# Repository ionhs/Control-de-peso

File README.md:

# PISU KONTROLA / CONTROL DE PESO

Este es el primer circuito que monta el alumnado de [Don Bosco](https://www.donbosco.eus/elektronika-mantentzen-lana/) en el ciclo de grado superior de Mantenimiento Electrónico. En vez de montar sobre una PCB, el alumnado lo monta sobre una protoboard.

Esto es parte del primer reto, en el que el alumnado sin ningún conocimiento previo ha de diseñar un sistema digital de control de peso con **4 sensores**. Cuanto más peso haya, se irán pulsando más botones hasta alcanzar la cantidad de peso optima, en el que se encenderá un **led verde.** En el caso que el peso no sea adecuado (por exceso o por defecto) se encenderá un **led rojo**. En el caso que la señal de entrada de los botones no sea lógica, se considerará que hay una avería que se indicará mediante un **led naraja**.

En este reto se busca que alumnado adquiera competencias y conocimientos en:

- Señales digitales 1/0 de entrada y de salida.

- Puertas lógicas (not, and, or...).

- Ecuaciones lógicas.

- Método de simplificación de ecuaciones con Karnaugh.

- Montaje y simulación de circuitos con puertas lógicas.

- Mantenimiento de circuitos con puertas lógicas.

El diseño ha sido realizado en [KiCad](https://www.kicad.org/), un software **open source**. Esto permite que cualquiera pueda replicar el proyecto o modificarlo según sus necesidades, facilitando su adaptación a otros usos educativos o personales.

## Puesta en marcha

Para hacer una demostración y la puesta en marcha hay que seguir los siguientes pasos:

1. Dejar la placa sobre la mesa, sin que ningún objeto metálico tenga contacto por la parte de abajo.

2. Mediante un cable usb conectar la placa a una fuente de alimentación usb o un portátil.

En este momento la placa ya es funcional por lo que se puede hacer la siguiente demostración de funcionamiento:

1. Pulsar el botón A y luego A y B a la vez para demostrar que con poco peso se enciende el diodo led de peso no adecuado.

2. Pulsar los botones A, B y C a la vez para demostrar que con peso adecuado se enciende el diodo led de peso adecuado.

3. Pulsar los cuatro botones a la vez para demostrar que con peso excesivo se enciende el diodo led de peso no adecuado.

4. Para demostrar la avería hay que pulsar alguna de las combinaciones imposibles como pulsar sólo B, sólo C, sólo D, sólo B y C a la vez, sólo B y D a la vez, sólo C y D a la vez o sólo B y C y D a la vez. En estos casos se encenderá avería y puede que algunos de los otros dos diodos leds. Como se enciende avería sólo se hace caso a la avería por lo que los otros led diodos no avisarían de nada.

Se puede mostrar la parte de electrónica analógica del reto. Para ello habría que tener una placa con resistencias en serie y paralelo que den 220 ohms de resistencia equivalente. Para conectarla hay que seguir estos pasos:

1. Quitar el jumper (JP1, JP2 o JP3) de la la resistencia interna de la placa que se quiere anular para conectar una equivalente por fuera.

2. Conectar al conector (J2, J3 o J4) la placa de resistencias equivalentes.

3. Probar los puntos 1, 2, 3, 4 de la demostración de funcionamiento.

4. 

## Puntos a mejorar

La placa de alimentación usb hay que ponerla por la parte de abajo para que vcc y gnd estén adecuadamente posicionada. Si se quiere que el USB esté por encima de la PCB habría que modificar el layout dándole la vuelta a la placa de alimentación USB y cambiando el routeo de los dos pads.

Además como mejora se puede diseñar una PCB de una fuente de alimentación de 5v. En la salida se pondría una placa de alimentación USB y mediante un cable, se podría conectar la placa de alimentación, al circuito del control de peso.

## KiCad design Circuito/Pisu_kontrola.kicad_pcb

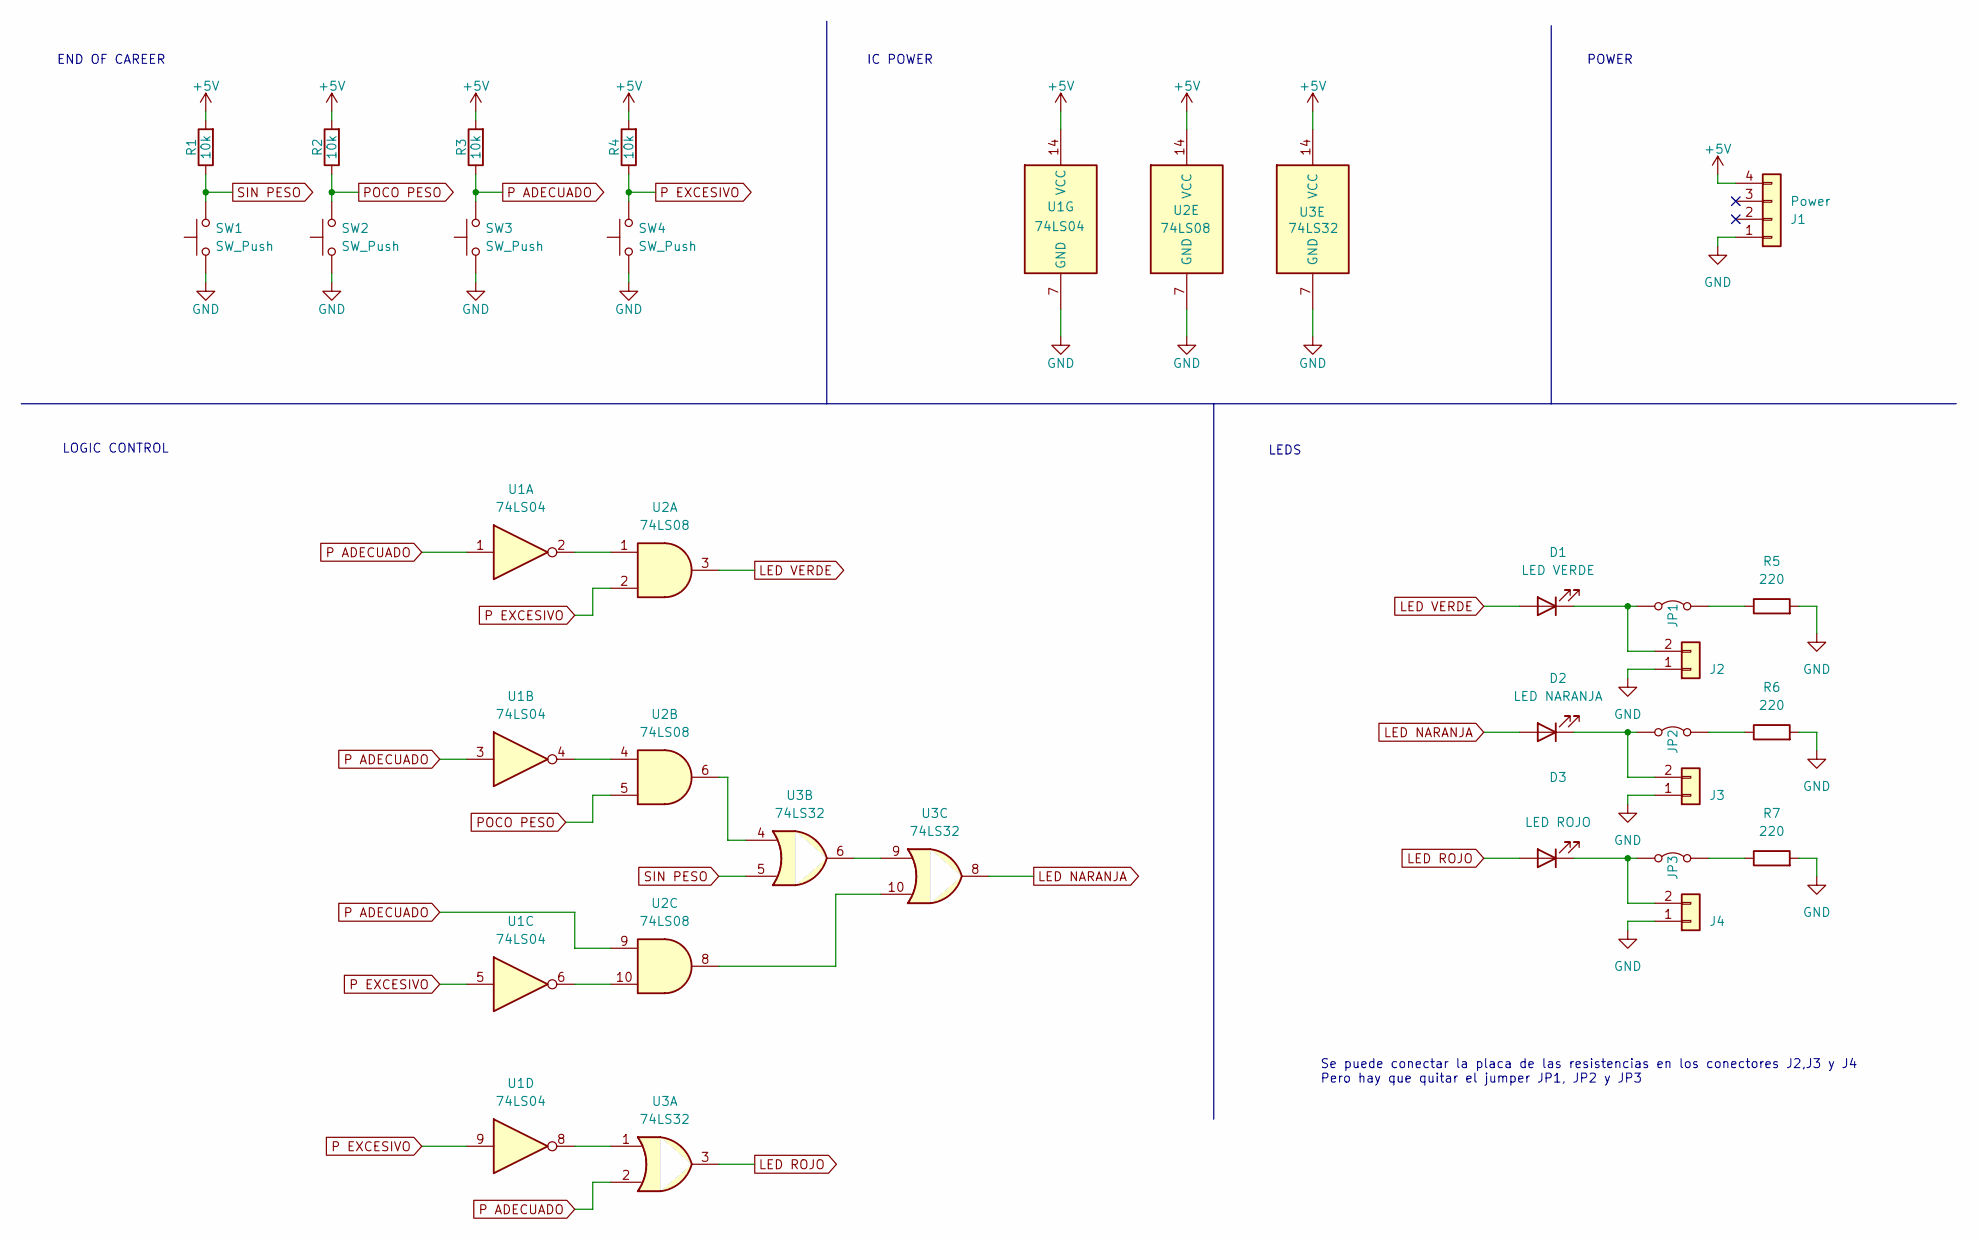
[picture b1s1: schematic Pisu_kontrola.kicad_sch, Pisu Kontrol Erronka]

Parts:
D1: LED VERDE; LED_D5.0mm
D2: LED NARANJA; LED_D5.0mm
D3: LED ROJO; LED_D5.0mm
J1: Power; USB -1x04_P2.54mm
J2, J3, J4: Conn_01x02; PinHeader_1x02_P2.54mm_Vertical
JP1, JP2, JP3: Jumper_2_Bridged; PinHeader_1x02_P2.54mm_Vertical
R1, R2, R3, R4: 10k; R_Axial_DIN0207_L6.3mm_D2.5mm_P10.16mm_Horizontal
R5, R6, R7: 220; R_Axial_DIN0207_L6.3mm_D2.5mm_P10.16mm_Horizontal
SW1, SW2, SW3, SW4: SW_Push; SW_PUSH-12mm
U1: 74LS04; DIP-14_W7.62mm
U2: 74LS08; DIP-14_W7.62mm
U3: 74LS32; DIP-14_W7.62mm

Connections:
+5V: J1.4, R1.2, R2.2, R3.2, R4.2, U1.14 (VCC), U2.14 (VCC), U3.14 (VCC)
GND: J1.1, J2.1, J3.1, J4.1, R5.2, R6.2, R7.2, SW1.1, SW2.1, SW3.1, SW4.1, U1.7 (GND), U2.7 (GND), U3.7 (GND)
LED NARANJA: D2.2 (A), U3.8
LED ROJO: D3.2 (A), U3.3
LED VERDE: D1.2 (A), U2.3
unnamed: D1.1 (K), J2.2, JP1.1 (A)
unnamed: D2.1 (K), J3.2, JP2.1 (A)
unnamed: D3.1 (K), J4.2, JP3.1 (A)
unnamed: JP1.2 (B), R5.1
unnamed: JP2.2 (B), R6.1
unnamed: JP3.2 (B), R7.1
unnamed: U1.2, U2.1
unnamed: U1.4, U2.4
unnamed: U1.6, U2.10
unnamed: U1.8, U3.1
unnamed: U2.6, U3.4
unnamed: U2.8, U3.10
unnamed: U3.6, U3.9
P ADECUADO: R3.1, SW3.2, U1.1, U1.3, U2.9, U3.2
P EXCESIVO: R4.1, SW4.2, U1.5, U1.9, U2.2
POCO PESO: R2.1, SW2.2, U2.5
SIN PESO: R1.1, SW1.2, U3.5

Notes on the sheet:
Se puede conectar la placa de las resistencias en los conectores J2,J3 y J4 Pero hay que quitar el jumper JP1, JP2 y JP3
LEDS
IC POWER
POWER
LOGIC CONTROL
END OF CAREER

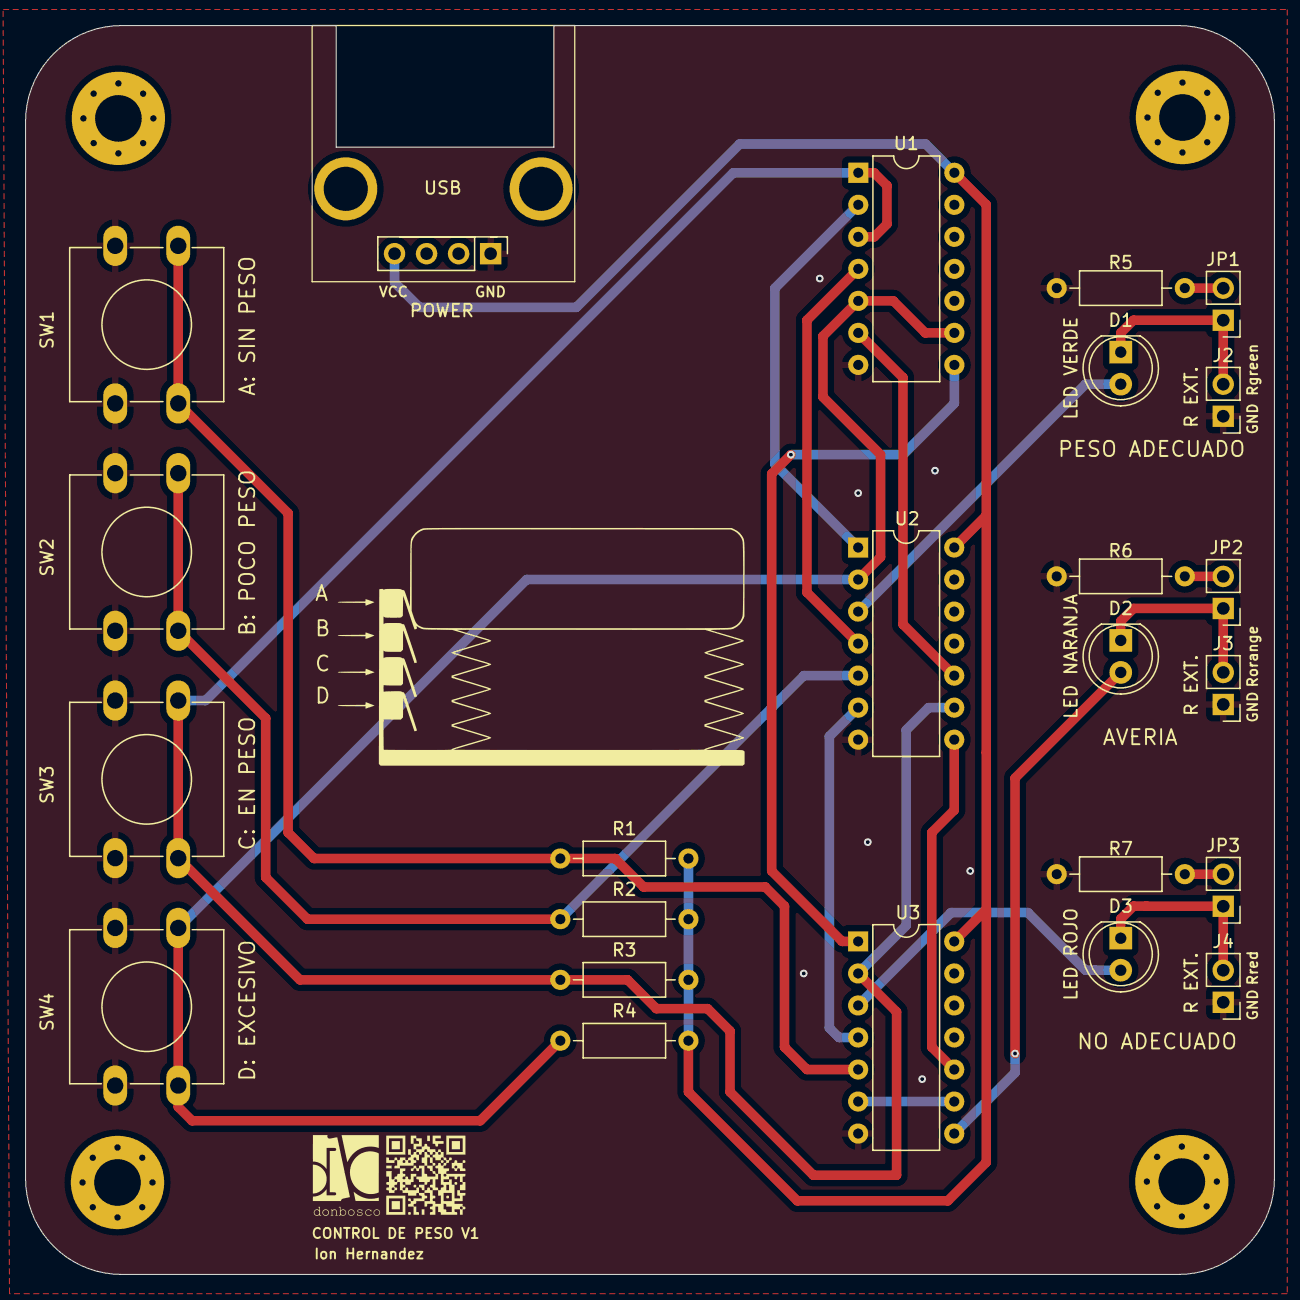
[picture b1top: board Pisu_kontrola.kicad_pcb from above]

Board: 2 copper layers, 99.1 x 99.1 mm, 24 parts (0 on the bottom side), 22 nets.

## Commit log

2025-02-06 Inicio del repositorio en local
2025-02-07 Readme actualización de enlaces

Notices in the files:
README.md:
License: CC BY-SA-4.0
